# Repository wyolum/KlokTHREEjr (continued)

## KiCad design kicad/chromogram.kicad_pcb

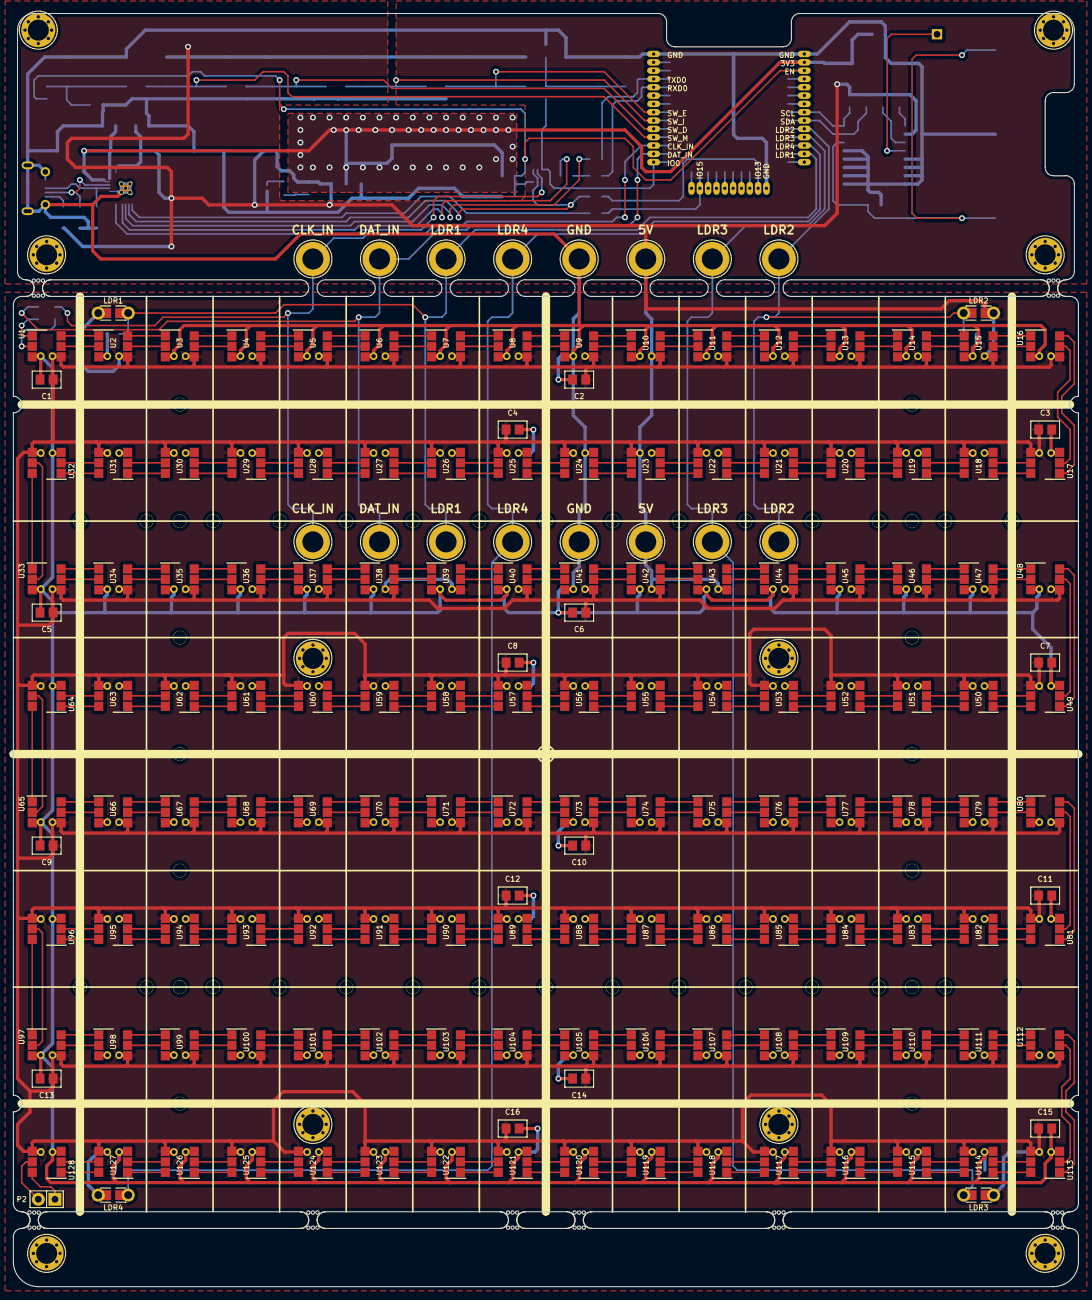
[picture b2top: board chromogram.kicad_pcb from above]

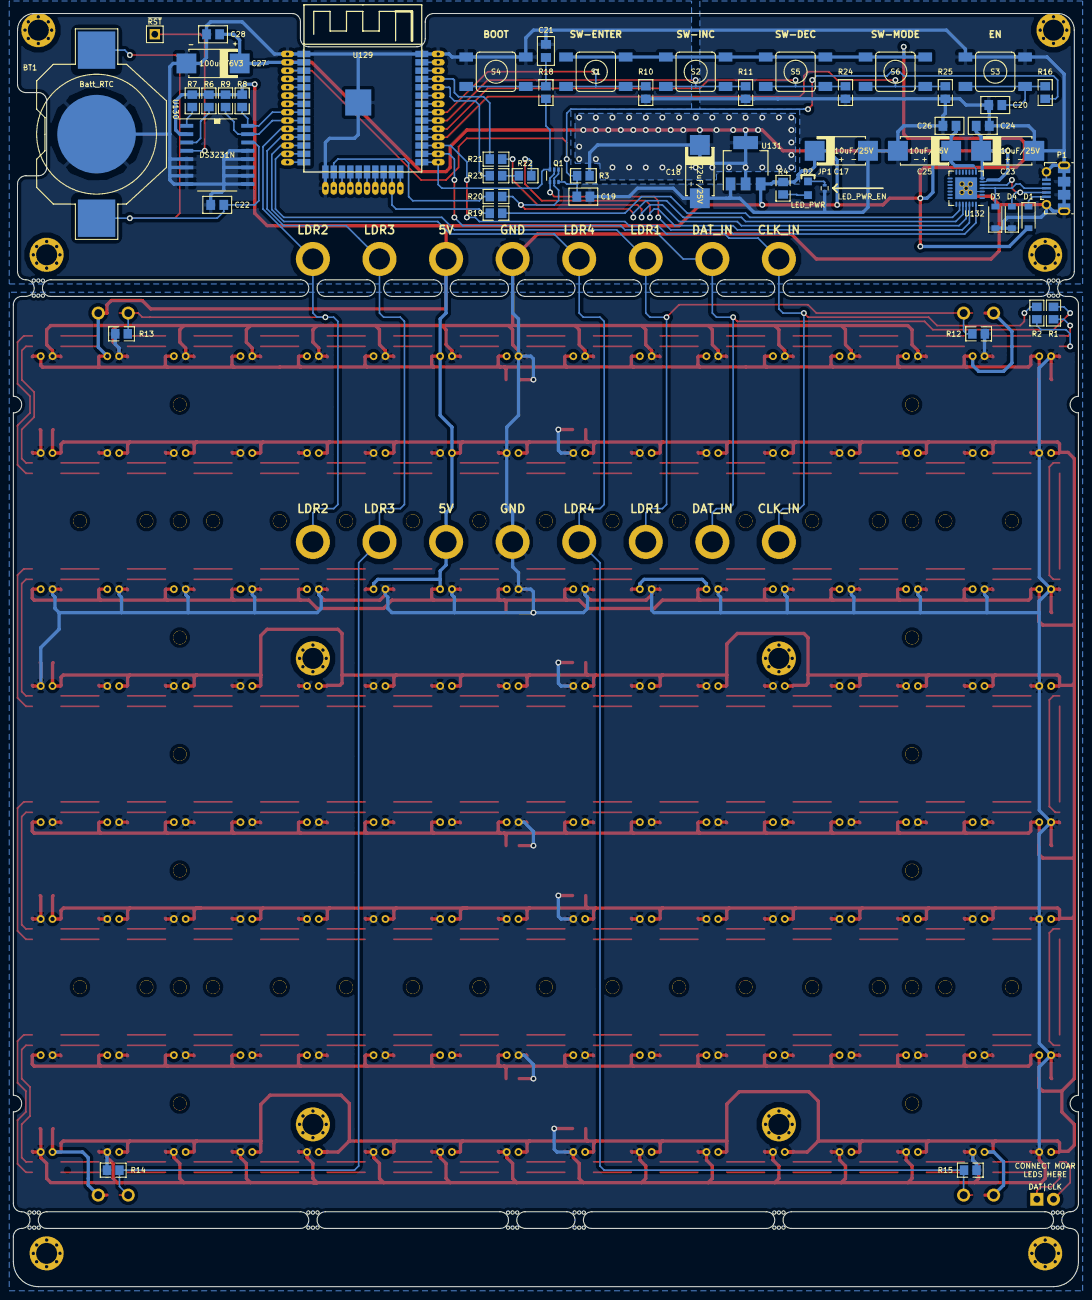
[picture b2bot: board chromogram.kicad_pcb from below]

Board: 2 copper layers, 162.6 x 194.3 mm, 281 parts (54 on the bottom side), 296 nets.

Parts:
BITE1, BITE2, BITE3, BITE4, BITE5, BITE6, BITE7, BITE8: Mouse_Bite; mouse-bite-2.54mm-slot
BT1: Batt_RTC; CR2032_SMD
C1, C2, C3, C4, C5, C6, C7, C8, C9, C10, C11, C12, C13, C14, C15, C16, C22, C24, C26: 100nF; c_0805
C17, C23, C25: 10uF/25V; c_2917
C18: 22uF/25V; c_2917
C19, C20, C21: 1nF; c_0805
C27: 100uF/6V3; c_2917
C28: 1uF/10V; c_0805
D1: 1N5819; D_SOD-123
D2: LED_PWR; LED-0805
D3, D4: VESD05A1B; D_SOD-123
HB1, HB2, HB3, HB4, HB5, HB6, HB7, HB8, HB9, HB10, HB11, HB12, HB13, HB14, HB15, HB16, HB17, HB18, HB19, HB20, HB21, HB22, HB23, HB24, HB25, HB26, HB27, HB28, HB29, HB30, HB31, HB32, HB33, HB34, HB35, HB36, HB37, HB38, HB39, HB40, HB41, HB42, HB43, HB44: hole_baffle; hole_baffle_2mm
HB45, HB46, HB47, HB48, HB49, HB50, HB51, HB52, HB53, HB54: hole_baffle; mtg_hole_3mm_vias_2
J1, J9: CLK_IN; 1pin
J2, J10: DAT_IN; 1pin
J3, J11: LDR1; 1pin
J4, J12: LDR2; 1pin
J5, J13: LDR3; 1pin
J6, J14: LDR4; 1pin
J7, J15: 5V; 1pin
J8, J16: GND; 1pin
JP1: LED_PWR_EN; R_0402
LDR1, LDR2, LDR3, LDR4: LDR; r_0805_ldr
P1: USB_micro; USB_Micro-B_Molex-105017-0001
P2: OUT_CLK_DAT; Pin_Header_Straight_1x02
Q1: DDC114TU; SOT-363_SC-70-6
R1, R2, R16, R18, R22: 470R; r_0805
R3: 10k; r_0805
R4: 2k; r_0805
R6, R7, R10, R11, R12, R13, R14, R15, R24, R25: 10K; r_0805
R8, R9: 4K7; r_0805
R19, R20: 0R NC; r_0805
R21, R23: 0R; r_0805
S1: SW-ENTER; SW_SMD
S2: SW-INC; SW_SMD
S3: EN; SW_SMD
S4: BOOT; SW_SMD
S5: SW-DEC; SW_SMD
S6: SW-MODE; SW_SMD
TP1: ~RST; BreakOutPad
U1, U2, U3, U4, U5, U6, U7, U8, U9, U10, U11, U12, U13, U14, U15, U16, U17, U18, U19, U20, U21, U22, U23, U24, U25, U26, U27, U28, U29, U30, U31, U32, U33, U34, U35, U36, U37, U38, U39, U40, U41, U42, U43, U44, U45, U46, U47, U48, U49, U50, U51, U52, U53, U54, U55, U56, U57, U58, U59, U60, U61, U62, U63, U64, U65, U66, U67, U68, U69, U70, U71, U72, U73, U74, U75, U76, U77, U78, U79, U80, U81, U82, U83, U84, U85, U86, U87, U88, U89, U90, U91, U92, U93, U94, U95, U96, U97, U98, U99, U100, U101, U102, U103, U104, U105, U106, U107, U108, U109, U110, U111, U112, U113, U114, U115, U116, U117, U118, U119, U120, U121, U122, U123, U124, U125, U126, U127, U128: APA102
U129: ESP-wroom-32; esp_wroom_32
U130: DS3231N; DS3231
U131: AP1117-15; SOT-223-3_TabPin2
U132: CP2102N-A01-GQFN28; QFN-28-1EP_5x5mm_Pitch0.5mm

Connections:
/3V3: C18.1, C23.1, C24.1, C27.1, C28.1, R3.1, U129.2, U131.2, U132.6, U132.7
/5V: C1.2, C2.2, C3.2, C4.2, C5.2, C6.2, C7.2, C8.2, C9.2, C10.2, C11.2, C12.2, C13.2, C14.2, C15.2, C16.2, C17.1, C25.1, C26.1, D1.2, J7.1, J15.1, LDR1.1, LDR2.1, LDR3.1, LDR4.1, R4.1, R6.1, R7.1, R8.1, R9.1, S1.1, S1.3, S2.1, S2.3, S5.1, S5.3, S6.1, S6.3, U1.4, U2.4, U3.4, U4.4, U5.4, U6.4, U7.4, U8.4, U9.4, U10.4, U11.4, U12.4, U13.4, U14.4, U15.4, U16.4, U17.4, U18.4, U19.4, U20.4, U21.4, U22.4, U23.4, U24.4, U25.4, U26.4, U27.4, U28.4, U29.4, U30.4, U31.4, U32.4, U33.4, U34.4, U35.4, U36.4, U37.4, U38.4, U39.4, U40.4, U41.4, U42.4, U43.4, U44.4, U45.4, U46.4, U47.4, U48.4, U49.4, U50.4, U51.4, U52.4, U53.4, U54.4, U55.4, U56.4, U57.4, U58.4, U59.4, U60.4, U61.4, U62.4, U63.4, U64.4, U65.4, U66.4, U67.4, U68.4, U69.4, U70.4, U71.4, U72.4, U73.4, U74.4, U75.4, U76.4, U77.4, U78.4, U79.4, U80.4, U81.4, U82.4, U83.4, U84.4, U85.4, U86.4, U87.4, U88.4, U89.4, U90.4, U91.4, U92.4, U93.4, U94.4, U95.4, U96.4, U97.4, U98.4, U99.4, U100.4, U101.4, U102.4, U103.4, U104.4, U105.4, U106.4, U107.4, U108.4, U109.4, U110.4, U111.4, U112.4, U113.4, U114.4, U115.4, U116.4, U117.4, U118.4, U119.4, U120.4, U121.4, U122.4, U123.4, U124.4, U125.4, U126.4, U127.4, U128.4, U130.2, U131.3, U132.8
/CI_A: R2.2, U1.2
/CI_B: U16.5, U17.2
/CI_C: U32.5, U33.2
/CI_D: U48.5, U49.2
/CI_E: U64.5, U65.2
/CI_F: U80.5, U81.2
/CI_G: U96.5, U97.2
/CI_H: U112.5, U113.2
/CLK_IN: J1.1, J9.1, R2.1, U129.27
/CLK_OUT: P2.2, U128.5
/DAT_IN: J2.1, J10.1, R1.1, U129.26
/DAT_OUT: P2.1, U128.6
/DI_A: R1.2, U1.1
/DI_B: U16.6, U17.1
/DI_C: U32.6, U33.1
/DI_D: U48.6, U49.1
/DI_E: U64.6, U65.1
/DI_F: U80.6, U81.1
/DI_G: U96.6, U97.1
/DI_H: U112.6, U113.1
/DTR: Q1.2, Q1.4, U132.28
/EN: C19.1, Q1.6, R3.2, R16.1, U129.3
/IO0: Q1.3, R18.1, U129.25
/IO13: R20.1, U129.16
/IO15: R19.1, U129.23
/LDR1: J3.1, J11.1, LDR1.2, R12.1, U129.13
/LDR2: J4.1, J12.1, LDR2.2, R13.1, U129.10
/LDR3: J5.1, J13.1, LDR3.2, R14.1, U129.11
/LDR4: J6.1, J14.1, LDR4.2, R15.1, U129.12
/RXD0: R23.1, U129.34
/SCL: R8.2, U129.8, U130.16
/SDA: R9.2, U129.9, U130.15
/SW_D: R24.1, S5.2, S5.4, U129.29
/SW_E: R10.1, S1.2, S1.4, U129.31
/SW_I: R11.1, S2.2, S2.4, U129.30
/SW_M: R25.1, S6.2, S6.4, U129.28
/TXD0: R21.1, U129.35
/esp_pwr_uart/CTS: R19.2, U132.23
/esp_pwr_uart/RTS: Q1.1, Q1.5, R20.2, U132.24
/esp_pwr_uart/RXD: R21.2, U132.25
/esp_pwr_uart/TXD: R22.1, R23.2
/esp_pwr_uart/USB_D+: D3.2, P1.3, U132.4
/esp_pwr_uart/USB_D-: D4.2, P1.2, U132.5
/rtc_ds3231/32kHz: R7.2, U130.1
/rtc_ds3231/BAT: BT1.1, C22.1, U130.14
/rtc_ds3231/RESET: TP1.1, U130.4
/rtc_ds3231/SQR: R6.2, U130.3
GND: BT1.2, C1.1, C2.1, C3.1, C4.1, C5.1, C6.1, C7.1, C8.1, C9.1, C10.1, C11.1, C12.1, C13.1, C14.1, C15.1, C16.1, C17.2, C18.2, C19.2, C20.2, C21.2, C22.2, C23.2, C24.2, C25.2, C26.2, C27.2, C28.2, D3.1, D4.1, J8.1, J16.1, JP1.1, P1.5, P1.6, R10.2, R11.2, R12.2, R13.2, R14.2, R15.2, R24.2, R25.2, S3.2, S3.4, S4.2, S4.4, U1.3, U2.3, U3.3, U4.3, U5.3, U6.3, U7.3, U8.3, U9.3, U10.3, U11.3, U12.3, U13.3, U14.3, U15.3, U16.3, U17.3, U18.3, U19.3, U20.3, U21.3, U22.3, U23.3, U24.3, U25.3, U26.3, U27.3, U28.3, U29.3, U30.3, U31.3, U32.3, U33.3, U34.3, U35.3, U36.3, U37.3, U38.3, U39.3, U40.3, U41.3, U42.3, U43.3, U44.3, U45.3, U46.3, U47.3, U48.3, U49.3, U50.3, U51.3, U52.3, U53.3, U54.3, U55.3, U56.3, U57.3, U58.3, U59.3, U60.3, U61.3, U62.3, U63.3, U64.3, U65.3, U66.3, U67.3, U68.3, U69.3, U70.3, U71.3, U72.3, U73.3, U74.3, U75.3, U76.3, U77.3, U78.3, U79.3, U80.3, U81.3, U82.3, U83.3, U84.3, U85.3, U86.3, U87.3, U88.3, U89.3, U90.3, U91.3, U92.3, U93.3, U94.3, U95.3, U96.3, U97.3, U98.3, U99.3, U100.3, U101.3, U102.3, U103.3, U104.3, U105.3, U106.3, U107.3, U108.3, U109.3, U110.3, U111.3, U112.3, U113.3, U114.3, U115.3, U116.3, U117.3, U118.3, U119.3, U120.3, U121.3, U122.3, U123.3, U124.3, U125.3, U126.3, U127.3, U128.3, U129.1, U129.15, U129.38, U129.39, U130.5, U130.6, U130.7, U130.8, U130.9, U130.10, U130.11, U130.12, U130.13, U131.1, U132.3, U132.29
unnamed: C20.1, R16.2, S3.1, S3.3
unnamed: C21.1, R18.2, S4.1, S4.3
unnamed: D1.1, P1.1
unnamed: D2.1, R4.2
unnamed: D2.2, JP1.2
unnamed: R22.2, U132.26
unnamed: U1.5, U2.2
unnamed: U1.6, U2.1
unnamed: U2.5, U3.2
unnamed: U2.6, U3.1
unnamed: U3.5, U4.2
unnamed: U3.6, U4.1
unnamed: U4.5, U5.2
unnamed: U4.6, U5.1
unnamed: U5.5, U6.2
unnamed: U5.6, U6.1
unnamed: U6.5, U7.2
unnamed: U6.6, U7.1
unnamed: U7.5, U8.2
unnamed: U7.6, U8.1
unnamed: U8.5, U9.2
unnamed: U8.6, U9.1
unnamed: U9.6, U10.1
unnamed: U9.5, U10.2
unnamed: U10.5, U11.2
unnamed: U10.6, U11.1
unnamed: U11.5, U12.2
unnamed: U11.6, U12.1
unnamed: U12.5, U13.2
unnamed: U12.6, U13.1
unnamed: U13.5, U14.2
unnamed: U13.6, U14.1
unnamed: U14.5, U15.2
unnamed: U14.6, U15.1
unnamed: U15.5, U16.2
unnamed: U15.6, U16.1
unnamed: U17.5, U18.2
unnamed: U17.6, U18.1
unnamed: U18.5, U19.2
unnamed: U18.6, U19.1
unnamed: U19.5, U20.2
unnamed: U19.6, U20.1
unnamed: U20.5, U21.2
unnamed: U20.6, U21.1
unnamed: U21.5, U22.2
unnamed: U21.6, U22.1
unnamed: U22.5, U23.2
unnamed: U22.6, U23.1
unnamed: U23.5, U24.2
unnamed: U23.6, U24.1
unnamed: U24.5, U25.2
unnamed: U24.6, U25.1
unnamed: U25.5, U26.2
unnamed: U25.6, U26.1
unnamed: U26.5, U27.2
unnamed: U26.6, U27.1
unnamed: U27.5, U28.2
unnamed: U27.6, U28.1
unnamed: U28.5, U29.2
unnamed: U28.6, U29.1
unnamed: U29.5, U30.2
unnamed: U29.6, U30.1
unnamed: U30.5, U31.2
unnamed: U30.6, U31.1
unnamed: U31.5, U32.2
unnamed: U31.6, U32.1
unnamed: U33.5, U34.2
unnamed: U33.6, U34.1
unnamed: U34.5, U35.2
unnamed: U34.6, U35.1
unnamed: U35.5, U36.2
unnamed: U35.6, U36.1
unnamed: U36.5, U37.2
unnamed: U36.6, U37.1
unnamed: U37.5, U38.2
unnamed: U37.6, U38.1
unnamed: U38.5, U39.2
unnamed: U38.6, U39.1
unnamed: U39.5, U40.2
unnamed: U39.6, U40.1
unnamed: U40.5, U41.2
unnamed: U40.6, U41.1
unnamed: U41.5, U42.2
unnamed: U41.6, U42.1
unnamed: U42.5, U43.2
unnamed: U42.6, U43.1
unnamed: U43.5, U44.2
unnamed: U43.6, U44.1
unnamed: U44.5, U45.2
unnamed: U44.6, U45.1
unnamed: U45.5, U46.2
unnamed: U45.6, U46.1
unnamed: U46.5, U47.2
unnamed: U46.6, U47.1
unnamed: U47.5, U48.2
unnamed: U47.6, U48.1
unnamed: U49.5, U50.2
unnamed: U49.6, U50.1
unnamed: U50.5, U51.2
unnamed: U50.6, U51.1
unnamed: U51.5, U52.2
unnamed: U51.6, U52.1
unnamed: U52.5, U53.2
unnamed: U52.6, U53.1
unnamed: U53.5, U54.2
unnamed: U53.6, U54.1
unnamed: U54.5, U55.2
unnamed: U54.6, U55.1
unnamed: U55.5, U56.2
unnamed: U55.6, U56.1
unnamed: U56.5, U57.2
unnamed: U56.6, U57.1
unnamed: U57.5, U58.2
unnamed: U57.6, U58.1
unnamed: U58.5, U59.2
unnamed: U58.6, U59.1
unnamed: U59.5, U60.2
unnamed: U59.6, U60.1
unnamed: U60.5, U61.2
unnamed: U60.6, U61.1
unnamed: U61.5, U62.2
unnamed: U61.6, U62.1
unnamed: U62.5, U63.2
unnamed: U62.6, U63.1
unnamed: U63.5, U64.2
unnamed: U63.6, U64.1
unnamed: U65.5, U66.2
unnamed: U65.6, U66.1
unnamed: U66.5, U67.2
unnamed: U66.6, U67.1
unnamed: U67.5, U68.2
unnamed: U67.6, U68.1
unnamed: U68.5, U69.2
unnamed: U68.6, U69.1
unnamed: U69.5, U70.2
unnamed: U69.6, U70.1
unnamed: U70.5, U71.2
unnamed: U70.6, U71.1
unnamed: U71.5, U72.2
unnamed: U71.6, U72.1
unnamed: U72.5, U73.2
unnamed: U72.6, U73.1
unnamed: U73.5, U74.2
unnamed: U73.6, U74.1
unnamed: U74.5, U75.2
unnamed: U74.6, U75.1
unnamed: U75.5, U76.2
unnamed: U75.6, U76.1
unnamed: U76.5, U77.2
unnamed: U76.6, U77.1
unnamed: U77.5, U78.2
unnamed: U77.6, U78.1
unnamed: U78.5, U79.2
unnamed: U78.6, U79.1
unnamed: U79.5, U80.2
unnamed: U79.6, U80.1
unnamed: U81.5, U82.2
unnamed: U81.6, U82.1
unnamed: U82.5, U83.2
unnamed: U82.6, U83.1
unnamed: U83.5, U84.2
unnamed: U83.6, U84.1
unnamed: U84.5, U85.2
unnamed: U84.6, U85.1
unnamed: U85.5, U86.2
unnamed: U85.6, U86.1
unnamed: U86.5, U87.2
unnamed: U86.6, U87.1
unnamed: U87.5, U88.2
unnamed: U87.6, U88.1
unnamed: U88.5, U89.2
unnamed: U88.6, U89.1
unnamed: U89.5, U90.2
unnamed: U89.6, U90.1
unnamed: U90.5, U91.2
unnamed: U90.6, U91.1
unnamed: U91.5, U92.2
unnamed: U91.6, U92.1
unnamed: U92.5, U93.2
unnamed: U92.6, U93.1
unnamed: U93.5, U94.2
unnamed: U93.6, U94.1
unnamed: U94.5, U95.2
unnamed: U94.6, U95.1
unnamed: U95.5, U96.2
unnamed: U95.6, U96.1
unnamed: U97.5, U98.2
unnamed: U97.6, U98.1
unnamed: U98.5, U99.2
unnamed: U98.6, U99.1
unnamed: U99.6, U100.1
unnamed: U99.5, U100.2
unnamed: U100.5, U101.2
unnamed: U100.6, U101.1
unnamed: U101.5, U102.2
unnamed: U101.6, U102.1
unnamed: U102.5, U103.2
unnamed: U102.6, U103.1
unnamed: U103.5, U104.2
unnamed: U103.6, U104.1
unnamed: U104.5, U105.2
unnamed: U104.6, U105.1
unnamed: U105.5, U106.2
unnamed: U105.6, U106.1
unnamed: U106.5, U107.2
unnamed: U106.6, U107.1
unnamed: U107.5, U108.2
unnamed: U107.6, U108.1
unnamed: U108.5, U109.2
unnamed: U108.6, U109.1
unnamed: U109.5, U110.2
unnamed: U109.6, U110.1
unnamed: U110.5, U111.2
unnamed: U110.6, U111.1
unnamed: U111.5, U112.2
unnamed: U111.6, U112.1
unnamed: U113.5, U114.2
unnamed: U113.6, U114.1
unnamed: U114.5, U115.2
unnamed: U114.6, U115.1
unnamed: U115.5, U116.2
unnamed: U115.6, U116.1
unnamed: U116.5, U117.2
unnamed: U116.6, U117.1
unnamed: U117.5, U118.2
unnamed: U117.6, U118.1
unnamed: U118.5, U119.2
unnamed: U118.6, U119.1
unnamed: U119.5, U120.2
unnamed: U119.6, U120.1
unnamed: U120.5, U121.2
unnamed: U120.6, U121.1
unnamed: U121.5, U122.2
unnamed: U121.6, U122.1
unnamed: U122.5, U123.2
unnamed: U122.6, U123.1
unnamed: U123.5, U124.2
unnamed: U123.6, U124.1
unnamed: U124.5, U125.2
unnamed: U124.6, U125.1
unnamed: U125.5, U126.2
unnamed: U125.6, U126.1
unnamed: U126.5, U127.2
unnamed: U126.6, U127.1
unnamed: U127.5, U128.2
unnamed: U127.6, U128.1

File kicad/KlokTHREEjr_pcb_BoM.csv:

"Id";"Designator";"Package";"Quantity";"Designation";"Supplier and ref";
1;"C27";"c_2917";1;"100uF/6V3";;;
2;"U133";"VSSOP-8_2.4x2.1mm_Pitch0.5mm";1;"TXB0102DCU";;;
3;"C29,C1,C2,C3,C4,C5,C6,C7,C8,C9,C10,C11,C12,C13,C14,C15,C16,C22,C24,C26,C30";"c_0805";21;"100nF";;;
4;"R25,R24,R6,R7,R10,R11,R12,R13,R14,R15,R3,R5";"r_0805";12;"10k";;;
5;"TP1";"BreakOutPad";1;"~RST";;;
6;"HB47,HB49,HB50,HB51,HB52,HB53,HB54,HB48";"MountingHole_3.2mm_M3_Pad_Via";8;"mtg_hole_3mm";;;
7;"HB46,HB45";"MountingHole_3.2mm_M3";2;"mtg_hole_3mm_small";;;
8;"J1,J9";"1pin";2;"CLK_IN";;;
9;"J2,J10";"1pin";2;"DAT_IN";;;
10;"J3,J11";"1pin";2;"LDR1";;;
11;"J4,J12";"1pin";2;"LDR2";;;
12;"J5,J13";"1pin";2;"LDR3";;;
13;"J6,J14";"1pin";2;"LDR4";;;
14;"J7,J15";"1pin";2;"5V";;;
15;"J8,J16";"1pin";2;"GND";;;
16;"BITE1,BITE2,BITE3,BITE4,BITE5,BITE6,BITE7,BITE8";"mouse-bite-2.54mm-slot_OSH";8;"Mouse_Bite";;;
17;"D1";"D_SOD-123";1;"1N5819";;;
18;"D3,D4";"D_LLP1006-2L";2;"VESD05A1B";;;
19;"BT1";"CR2032_SMD2";1;"Batt_RTC";;;
20;"P2";"Pin_Header_Straight_1x02";1;"OUT_CLK_DAT";;;
21;"U132";"QFN-28-1EP_5x5mm_Pitch0.5mm";1;"CP2102N-A01-GQFN28";;;
22;"JP1";"R_0402";1;"LED_PWR_EN";;;
23;"D2";"LED-0805";1;"LED_PWR";;;
24;"U130";"DS3231";1;"DS3231N";;;
25;"LDR1,LDR4,LDR3,LDR2";"r_0805_ldr";4;"LDR";;;
26;"U127,U18,U1,U3,U4,U5,U6,U7,U8,U9,U10,U11,U12,U13,U14,U15,U16,U17,U19,U20,U21,U22,U23,U24,U25,U26,U27,U28,U29,U30,U31,U32,U33,U34,U35,U36,U37,U38,U39,U40,U41,U42,U43,U44,U45,U46,U47,U48,U49,U50,U51,U52,U53,U54,U55,U56,U57,U58,U59,U60,U61,U62,U63,U64,U65,U66,U67,U68,U69,U70,U71,U72,U73,U74,U75,U76,U77,U78,U79,U80,U81,U82,U83,U84,U85,U86,U87,U88,U89,U90,U91,U92,U93,U94,U95,U96,U97,U98,U99,U100,U101,U102,U103,U104,U105,U106,U107,U108,U109,U110,U111,U112,U113,U114,U115,U116,U117,U118,U119,U120,U121,U122,U123,U124,U125,U126,U128,U2";"APA102";128;"APA102";;;
27;"S1";"SW_SMD";1;"SW-ENTER";;;
28;"S2";"SW_SMD";1;"SW-INC";;;
29;"S3";"SW_SMD";1;"EN";;;
30;"S4";"SW_SMD";1;"BOOT";;;
31;"S5";"SW_SMD";1;"SW-DEC";;;
32;"S6";"SW_SMD";1;"SW-MODE";;;
33;"P1";"USB_Micro-B_Molex-105017-0001";1;"USB_micro";;;
34;"R1,R2,R16,R18,R22";"r_0805";5;"470R";;;
35;"R8,R9";"r_0805";2;"4K7";;;
36;"HB44,HB43,HB42,HB41,HB40,HB39,HB38,HB37,HB36,HB35,HB34,HB33,HB32,HB31,HB30,HB29,HB28,HB27,HB26,HB25,HB24,HB23,HB22,HB21,HB20,HB19,HB18,HB17,HB16,HB15,HB14,HB13,HB12,HB11,HB10,HB9,HB8,HB7,HB6,HB5,HB4,HB3,HB2,HB1";"hole_baffle_2mm";44;"hole_baffle";;;
37;"C17,C23,C25";"c_2917";3;"10uF/25V";;;
38;"C18";"c_2917";1;"22uF/25V";;;
39;"C19,C20,C21";"c_0805";3;"1nF";;;
40;"C28";"c_0805";1;"1uF/10V";;;
41;"Q1";"SOT-363_SC-70-6";1;"DDC114TU";;;
42;"R4";"r_0805";1;"1k";;;
43;"R19,R20";"r_0805";2;"0R NC";;;
44;"R21,R23";"r_0805";2;"0R";;;
45;"U131";"SOT-223-3_TabPin2";1;"1117-33";;;
46;"U129";"esp_wroom_32";1;"ESP-wroom-32";;;
47;"G1,G4";"Logo-WL3";2;"LOGO_WL";;;
48;"G2,G5";"KiCad-Logo2_6mm_SilkScreen";2;"KiCad";;;
49;"G3,G6";"OSHW_6mm";2;"OSHW";;;

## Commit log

2017-12-24 first push
2017-12-24 edit readme
2017-12-25 working on ESP function list, see spreadsheet
2017-12-27 schematic WIP
2017-12-27 schematic dev in progress
2017-12-28 making progress on schematic
2017-12-29 WIP schematic
2017-12-29 making progress on PCB
2017-12-30 WIP PCB layout
2017-12-30 almost done with PCB
2017-12-31 PCB cleanup
2018-01-02 minor edits
2018-01-02 library edits
2018-01-03 modified diode footprints
2018-01-03 legend cleanup
2018-01-04 minor cleanup
2018-01-05 edited mousebites
2018-01-06 modified mounting holes
2018-01-06 added Gerbers
2018-01-07 renamed all files, fresh Gerbers
2018-01-07 added Gerber ZIP
2018-01-07 add FastLED library and example on wemos
2018-01-08 add firstlight example
2018-01-08 fresh gerbers and pdf after minor cleanup
2018-01-08 corrected error in pin assignments
2018-01-08 added keepout area under ESP antenna when boards are stacked
2018-01-09 added voltage translation ckt for I2C 3V3 to 5V
2018-01-10 removed voltage translation ckt for I2C, added I2C header
2018-01-11 started 8x8 prototype baffles
2018-01-11 added I2C and SPI headers
2018-01-11 tracks cleanup
2018-01-13 more tracks cleanup
2018-01-13 starting Arduino code for K3jr
2018-01-15 updated baffles for desklok
2018-01-16 testing desKlok with huzzah
2018-01-16 missing from repo:
    Adafruit_IO_Arduino (added)
    Adafruit_MQTT_Library (added)
    ArduinoHTTPClient (added)
    EEPROMAnything (added)
    I installed local copies here.
    also missing
2018-01-17 added NTP Client Lib
2018-01-17 Changed to use NTPClient lib
2018-01-18 Converted proto version to Huzzah
2018-01-19 changed baffle height
2018-01-21 update desKlok (inspired by Dulles)
2018-01-21 cleared usb cable on desKlok
2018-01-21 added Dulles DesKloK assembly photos
2018-01-22 1. git added MatrixMaps.h to libraries (including ULTIM*x16) 2. added credentials/README file with credentials.h template I also added the lines: #ifndef __CREDENTIALS_H #define __CREDENTIALS_H ... #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
    to the README template. This will prevent multiple declarations error.
    3. Cleaned up calls to Adafruit MQTT library that are no longer used.
2018-01-22 minor update
2018-01-23 added DesKlok image to README
2018-01-23 add template credentials.h
2018-01-23 add gitignore
2018-01-23 template credentials.h
2018-01-23 add global .gitignore
2018-01-23 add macros for duplicate need for wifi ssid and pass
2018-01-23 moved FLIP_DISPLAY to config.h
2018-01-23 added _anool enclosure in fabricate
2018-01-23 remove credentials.h template
2018-01-23 fix brightness bug, never changes
2018-01-23 Desk Klok housing, annol's version
2018-01-24 modified _anool enclosure in fabricate
2018-01-24 updated anool's DesKLOK version
2018-01-24 figuring git out... thanks Kevin and Anool
2018-01-25 added word drop in
2018-01-26 Desk Klok housing, anool's version, flex box
2018-01-28 worked on animations
2018-01-28 DesKLOK 3d print version modified
2018-01-29 abstracted display types for easier switching
2018-01-29 Anool, added missing language files to arduino/KlokTHREEjr_v2
2018-01-30 KlokTHREEjr_v2 now changed modes every hour.
2018-01-30 Anool, DesKLOK laser version files modified
2018-02-01 added ada.io control for display_idx: 0 word drop; 1 wipe around; 2 TheMatrix
2018-02-02 fix sense of adaIO inclusion
2018-02-03 copied dev program to production directory
2018-02-03 Copied dev version of Klok to DesKlok
2018-02-03 Anool, added dulles clock renders
2018-02-04 Anool, new baffle design
2018-02-04 renamed some files to match arduino conventions
2018-02-04 git added files
2018-02-07 Anool, added k3jr_controller_kicad folder/files
2018-02-08 Anool, updated controller board BoM
2018-02-08 Anool, updated KlokTHREEjr main board BoM
2018-02-09 Anool, enclosure update
2018-02-09 Anool, enclosure update 2
2018-02-11 added wifi manager and thingsboard to KlokTHREEjr_v3 still need add controls
2018-02-11 saved display preference in eeprom config in KlokTHREEjr_v3
2018-02-16 added splash screen to Klok
2018-03-03 add Kontroller Hardware test
2018-03-05 corrected I2C silk legend
2018-03-09 changed I2C connections
2018-03-09 kontroller layout modified. Old layout archived as rev _v1
2018-03-09 pulling new Kontroller
2018-03-10 K3jr schematic modified
2018-03-10 correction to Kontroller and KlockTHREEjr
2018-03-10 KlokTHREEjr final. Kontroller pending
2018-03-11 Kontroller layout/Gerber final
2018-03-11 seeed format BoM ready
2018-03-11 converted const PROGMEM faceplate to Faceplate class
2018-03-11 BoM minor correction
2018-03-11 refectoring web_server clock
2018-03-11 update NTP_clock so at least it is working
2018-03-11 added ds3231 clock
2018-03-17 USB protection, LDR, Switches reconfigured
2018-03-17 change clock() to clock_loop()
2018-03-18 ready for seeed submission
2018-03-18 re-write xls bom for compatibility
2018-03-18 move ldr to dnp
2018-03-18 renumber rows
2018-03-19 moved APA102 to DNP row on BoM
2018-03-21 coin battery footprint update - remove solder paste opening
2018-03-21 added Kontroller_v2 based on most recent KlokTHREEjr
2020-11-29 changed 'clock' to 'desk_clock'
